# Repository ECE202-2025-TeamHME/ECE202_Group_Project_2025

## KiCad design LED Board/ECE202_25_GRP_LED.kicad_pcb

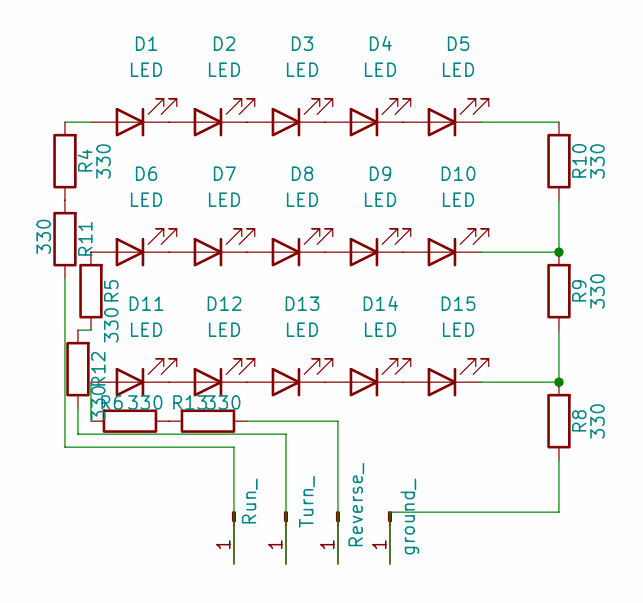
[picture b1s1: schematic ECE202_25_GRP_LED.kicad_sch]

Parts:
D1, D2, D3, D4, D5, D6, D7, D8, D9, D10, D11, D12, D13, D14, D15: LED; LED_1206_3216Metric_Pad1.42x1.75mm_HandSolder
J13: Run_; PinHeader_1x01_P2.54mm_Vertical
J14: Turn_; PinHeader_1x01_P2.54mm_Vertical
J15: Reverse_; PinHeader_1x01_P2.54mm_Vertical
J16: ground_; PinHeader_1x01_P2.54mm_Vertical
R4, R5, R6, R8, R9, R10, R11, R12, R13: 330; R_1206_3216Metric_Pad1.30x1.75mm_HandSolder

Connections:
unnamed: D1.2 (A), R4.2
unnamed: D1.1 (K), D2.2 (A)
unnamed: D2.1 (K), D3.2 (A)
unnamed: D3.1 (K), D4.2 (A)
unnamed: D4.1 (K), D5.2 (A)
unnamed: D5.1 (K), R10.2
unnamed: D6.2 (A), R5.2
unnamed: D6.1 (K), D7.2 (A)
unnamed: D7.1 (K), D8.2 (A)
unnamed: D8.1 (K), D9.2 (A)
unnamed: D9.1 (K), D10.2 (A)
unnamed: D10.1 (K), R9.2, R10.1
unnamed: D11.2 (A), R6.2
unnamed: D11.1 (K), D12.2 (A)
unnamed: D12.1 (K), D13.2 (A)
unnamed: D13.1 (K), D14.2 (A)
unnamed: D14.1 (K), D15.2 (A)
unnamed: D15.1 (K), R8.2, R9.1
unnamed: J13.1, R11.1
unnamed: J14.1, R12.1
unnamed: J15.1, R13.1
unnamed: J16.1, R8.1
unnamed: R4.1, R11.2
unnamed: R5.1, R12.2
unnamed: R6.1, R13.2

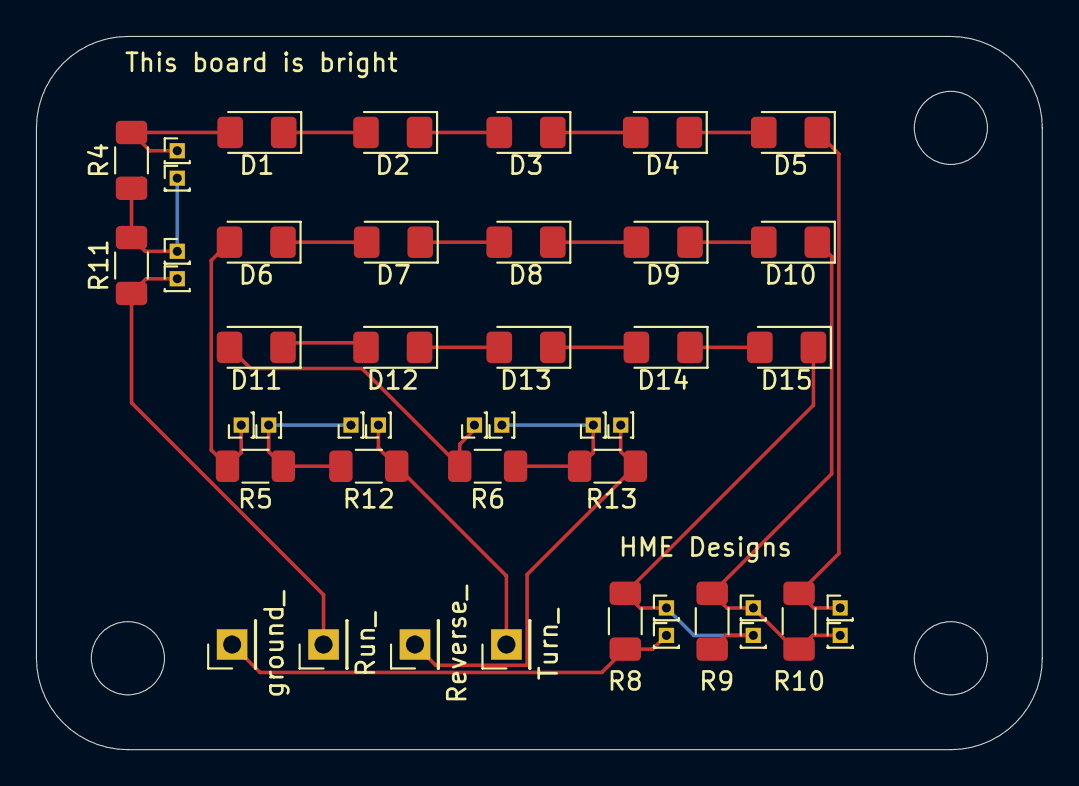
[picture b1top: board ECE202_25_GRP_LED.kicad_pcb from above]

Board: 2 copper layers, 55.9 x 39.6 mm, 28 parts (0 on the bottom side), 25 nets.

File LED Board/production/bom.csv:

Designator,Footprint,Quantity,Value,LCSC Part #
"D1, D10, D11, D12, D13, D14, D15, D2, D3, D4, D5, D6, D7, D8, D9",1206,15,LED,
J13,PinHeader_1x01_P2.54mm_Vertical,1,Run_,
J14,PinHeader_1x01_P2.54mm_Vertical,1,Turn_,
J15,PinHeader_1x01_P2.54mm_Vertical,1,Reverse_,
J16,PinHeader_1x01_P2.54mm_Vertical,1,ground_,
"R10, R11, R12, R13, R4, R5, R6, R8, R9",1206,9,330,

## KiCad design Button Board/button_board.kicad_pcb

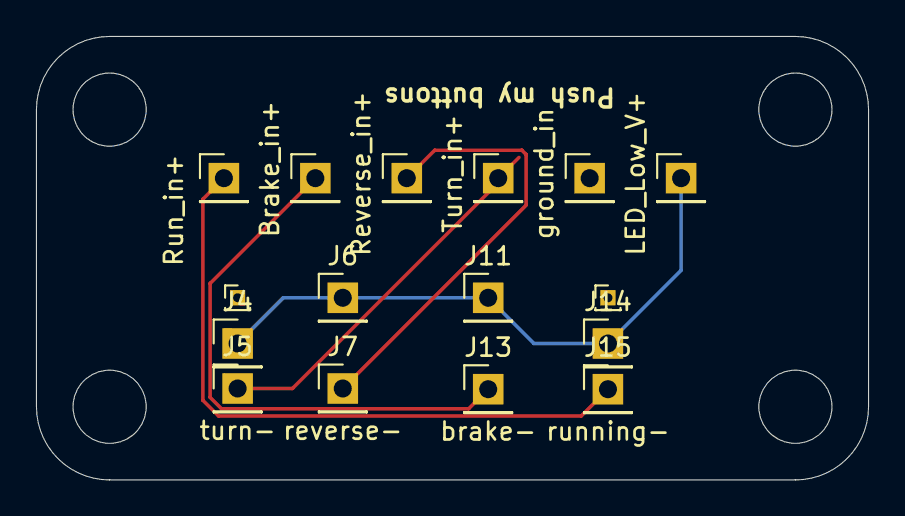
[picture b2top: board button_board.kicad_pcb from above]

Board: 2 copper layers, 46.2 x 24.6 mm, 16 parts (0 on the bottom side), 5 nets.

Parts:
J1: Run_in+; PinHeader_1x01_P2.54mm_Vertical
J2: Brake_in+; PinHeader_1x01_P2.54mm_Vertical
J3: Turn_in+; PinHeader_1x01_P2.54mm_Vertical
J4: turn+; PinHeader_1x01_P2.54mm_Vertical
J4#2: turn+; PinHeader_1x01_P1.00mm_Vertical
J5: turn-; PinHeader_1x01_P2.54mm_Vertical
J6: reverse+; PinHeader_1x01_P2.54mm_Vertical
J7: reverse-; PinHeader_1x01_P2.54mm_Vertical
J8: ground_in; PinHeader_1x01_P2.54mm_Vertical
J10: Reverse_in+; PinHeader_1x01_P2.54mm_Vertical
J11: brake+; PinHeader_1x01_P2.54mm_Vertical
J12: LED_Low_V+; PinHeader_1x01_P2.54mm_Vertical
J13: brake-; PinHeader_1x01_P2.54mm_Vertical
J14: running+; PinHeader_1x01_P1.00mm_Vertical
J14#2: running+; PinHeader_1x01_P2.54mm_Vertical
J15: running-; PinHeader_1x01_P2.54mm_Vertical

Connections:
unnamed: J1.1, J15.1
unnamed: J3.1, J5.1
unnamed: J7.1, J10.1
unnamed: J4.1, J6.1, J11.1, J12.1, J14#2.1
unnamed: J2.1, J13.1

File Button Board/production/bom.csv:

Designator,Footprint,Quantity,Value,LCSC Part #
J1,PinHeader_1x01_P2.54mm_Vertical,1,Run_in+,
J10,PinHeader_1x01_P2.54mm_Vertical,1,Reverse_in+,
J11,PinHeader_1x01_P2.54mm_Vertical,1,brake+,
J12,PinHeader_1x01_P2.54mm_Vertical,1,LED_Low_V+,
J13,PinHeader_1x01_P2.54mm_Vertical,1,brake-,
J14_2,PinHeader_1x01_P2.54mm_Vertical,1,running+,
J14,PinHeader_1x01_P1.00mm_Vertical,1,running+,
J15,PinHeader_1x01_P2.54mm_Vertical,1,running-,
J2,PinHeader_1x01_P2.54mm_Vertical,1,Brake_in+,
J3,PinHeader_1x01_P2.54mm_Vertical,1,Turn_in+,
J4_2,PinHeader_1x01_P2.54mm_Vertical,1,turn+,
J4,PinHeader_1x01_P1.00mm_Vertical,1,turn+,
J5,PinHeader_1x01_P2.54mm_Vertical,1,turn-,
J6,PinHeader_1x01_P2.54mm_Vertical,1,reverse+,
J7,PinHeader_1x01_P2.54mm_Vertical,1,reverse-,
J8,PinHeader_1x01_P2.54mm_Vertical,1,ground_in,

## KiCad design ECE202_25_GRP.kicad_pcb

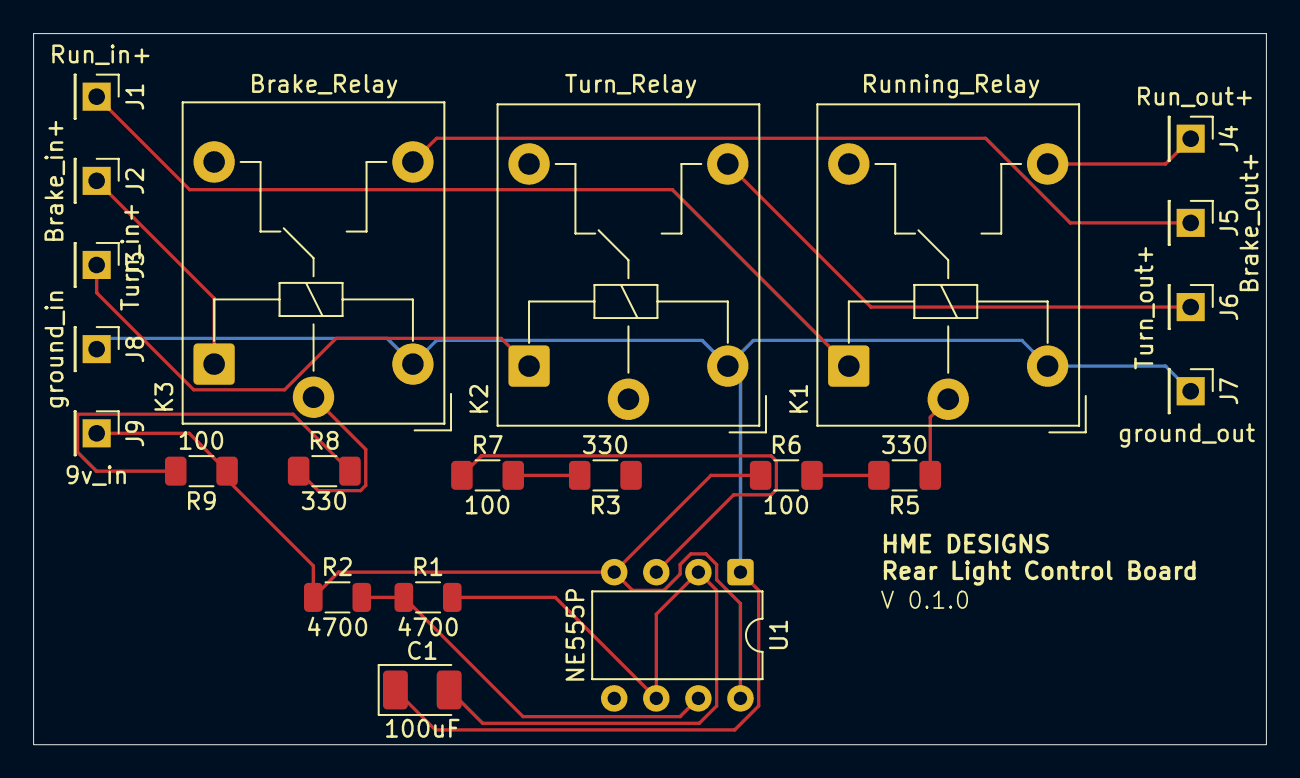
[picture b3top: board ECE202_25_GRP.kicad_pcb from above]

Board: 2 copper layers, 74.4 x 42.9 mm, 22 parts (0 on the bottom side), 17 nets.

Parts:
C1: 100uF; CP_EIA-3528-12_Kemet-T_Pad1.50x2.35mm_HandSolder
J1: Run_in+; PinHeader_1x01_P2.54mm_Vertical
J2: Brake_in+; PinHeader_1x01_P2.54mm_Vertical
J3: Turn_in+; PinHeader_1x01_P2.54mm_Vertical
J4: Run_out+; PinHeader_1x01_P2.54mm_Vertical
J5: Brake_out+; PinHeader_1x01_P2.54mm_Vertical
J6: Turn_out+; PinHeader_1x01_P2.54mm_Vertical
J7: ground_out; PinHeader_1x01_P2.54mm_Vertical
J8: ground_in; PinHeader_1x01_P2.54mm_Vertical
J9: 9v_in; PinHeader_1x01_P2.54mm_Vertical
K1: Running_Relay; Relay_SPDT_Hongfa_JQC-3FF_0XX-1Z
K2: Turn_Relay; Relay_SPDT_Hongfa_JQC-3FF_0XX-1Z
K3: Brake_Relay; Relay_SPDT_Hongfa_JQC-3FF_0XX-1Z
R1, R2: 4700; R_1206_3216Metric
R3, R5, R8: 330; R_1206_3216Metric_Pad1.30x1.75mm_HandSolder
R6, R7, R9: 100; R_1206_3216Metric_Pad1.30x1.75mm_HandSolder
U1: NE555P; DIP-8_W7.62mm

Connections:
+9V: J9.1, R2.1, R6.1, R9.1, U1.4 (R), U1.8 (VCC)
GND: C1.1, J7.1, J8.1, K1.A2, K2.A2, K3.A2, U1.1 (GND)
unnamed: J1.1, K1.A1
unnamed: J2.1, K3.A1
unnamed: J3.1, K2.A1
unnamed: J4.1, K1.14
unnamed: J5.1, K3.14
unnamed: J6.1, K2.14
unnamed: K1.11, R5.1
unnamed: K2.11, R3.1
unnamed: K3.11, R8.1
unnamed: R3.2, R7.2
unnamed: R5.2, R6.2
unnamed: R8.2, R9.2
unnamed: R1.1, R2.2, U1.7 (DIS)
unnamed: R7.1, U1.3 (Q)
unnamed: C1.2, R1.2, U1.2 (TR), U1.6 (THR)

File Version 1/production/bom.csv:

Designator,Footprint,Quantity,Value,LCSC Part #
C1,CP_EIA-3528-12_Kemet-T_Pad1.50x2.35mm_HandSolder,1,100uF,
J1,PinHeader_1x01_P2.54mm_Vertical,1,Run_in+,
J2,PinHeader_1x01_P2.54mm_Vertical,1,Brake_in+,
J3,PinHeader_1x01_P2.54mm_Vertical,1,Turn_in+,
J4,PinHeader_1x01_P2.54mm_Vertical,1,Run_out+,
J5,PinHeader_1x01_P2.54mm_Vertical,1,Brake_out+,
J6,PinHeader_1x01_P2.54mm_Vertical,1,Turn_out+,
J7,PinHeader_1x01_P2.54mm_Vertical,1,ground_out,
J8,PinHeader_1x01_P2.54mm_Vertical,1,ground_in,
J9,PinHeader_1x01_P2.54mm_Vertical,1,9v_in,
K1,Relay_SPDT_Hongfa_JQC-3FF_0XX-1Z,1,Running_Relay,
K2,Relay_SPDT_Hongfa_JQC-3FF_0XX-1Z,1,Turn_Relay,
K3,Relay_SPDT_Hongfa_JQC-3FF_0XX-1Z,1,Brake_Relay,
"R1, R2",1206,2,4700,
"R3, R5, R8",1206,3,330,
"R6, R7, R9",1206,3,100,
U1,DIP-8_W7.62mm,1,NE555P,

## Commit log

2025-03-12 idk what changed
2025-03-12 Early schematic Progress
2025-03-12 test update
2025-03-18 Finished V1 of schematic
    Screen shot in new images folder
2025-03-18 Schematic Repairs, v1 PCB
    Replaced bus with wires in schematic, added footprints to resistors, caps, pins in schematic.
    Imported schematic into PCB, designed PCB.
2025-03-18 PCB Production
    Production files generated, order screenshot added to images folder. PCB order started today 3-18-25
2025-03-30 V1 pcb updates, V2 pcb creation
    Fixed a couple traces on V1 board, added missing ground pin. Changed pad sizes for SMD components to match on-hand inventory.
    Created V2 project. Schematic done, PCB done. PCB ordered.
2025-03-30 Button PCB Creation
    Created button board schematic and PCB. Created build file. Sent to production.
2025-03-31 Project Folder Structure fixes
    put V1 into its own folder
2025-04-07 LED Board, practice board, button board updates
    Created led board and practice board/business card. Updated mounting for buttons on button board. Submitted all 3 for production on 4/6/25
2025-04-07 Pictures
    Added PCB photos of recently finished designs.
